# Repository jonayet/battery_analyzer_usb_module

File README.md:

battery_analyzer_usb_module
==============================

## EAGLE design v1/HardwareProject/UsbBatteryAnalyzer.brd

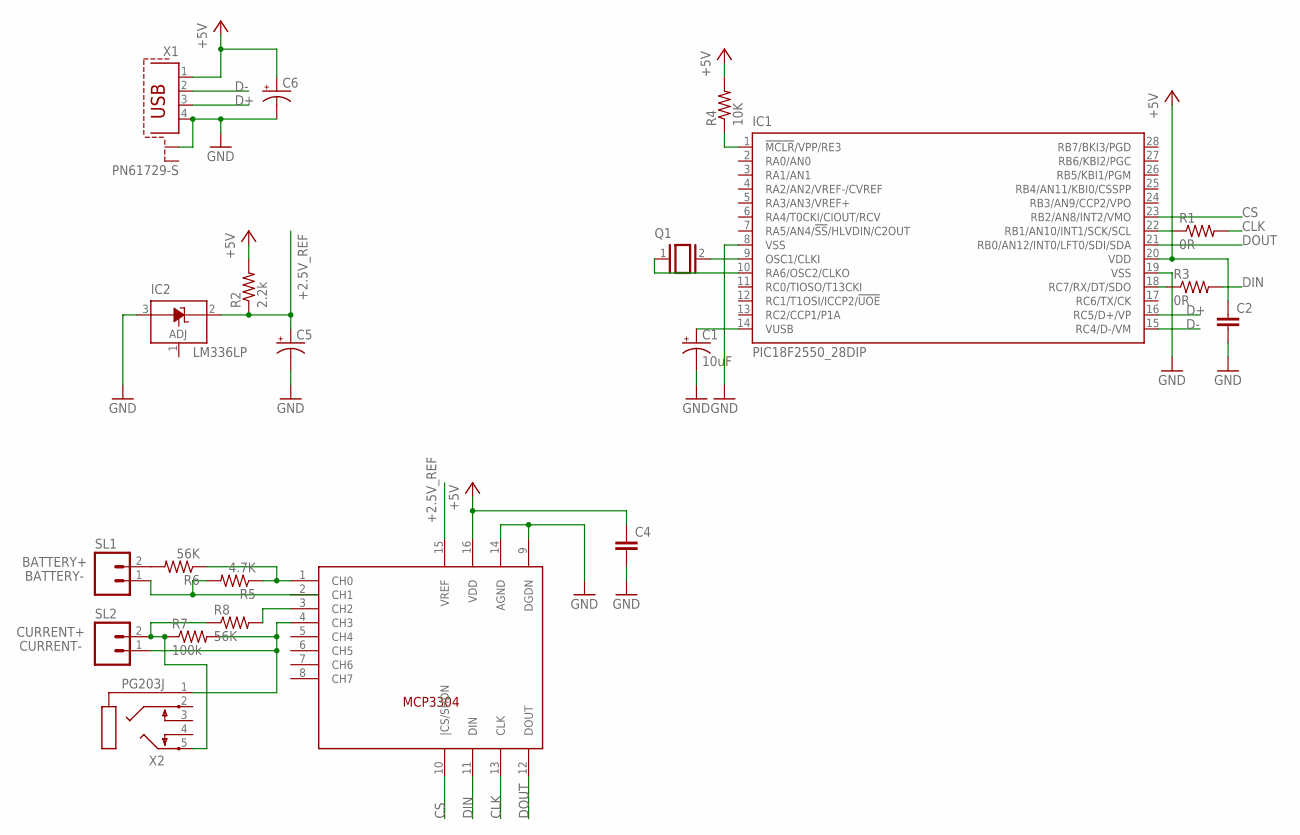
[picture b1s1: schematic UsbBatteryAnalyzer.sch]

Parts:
C1: 10uF; E2,5-7
C2, C4: C-EU050-024X044; C050-024X044
C5, C6: CPOL-USE2.5-7; E2,5-7
IC1: PIC18F2550_28DIP; DIL28-3
IC2: LM336LP; TO92
Q1: XTAL/S; QS
R1: 0R; 0207/5V
R2: 2.2k; 0204/7
R3: 0R; 0207/10
R4: 10K; 0204/7
R5: 4.7K; 0204/7
R6, R8: 56K; 0204/7
R7: 100k; 0204/7
SL1, SL2: M02; 02P
U$1: MCP3304; DIP16
X1: PN61729-S
X2: PG203J

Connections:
+2.5V_REF: C5.+, IC2.2 (C), R2.1, U$1.15 (VREF)
+5V: C2.1, C4.1, C6.+, IC1.20 (VDD), R2.2, R4.2, U$1.16 (VDD), X1.1
BATTERY+: R6.2, SL1.2
BATTERY-: R5.2, SL1.1, U$1.2 (CH1)
CLK: R1.2, U$1.13 (CLK)
CS: IC1.23 (RB2/AN8/INT2/VMO), U$1.10 (|CS/SHDN)
CURRENT+: R7.1, R8.1, SL2.2, X2.5
CURRENT-: R7.2, SL2.1, U$1.4 (CH3), X2.1
D+: IC1.16 (RC5/D+/VP), X1.3
D-: IC1.15 (RC4/D-/VM), X1.2
DIN: R3.2, U$1.11 (DIN)
DOUT: IC1.21 (RB0/AN12/INT0/LFT0/SDI/SDA), U$1.12 (DOUT)
GND: C1.-, C2.2, C4.2, C5.-, C6.-, IC1.8 (VSS), IC1.19 (VSS), IC2.3 (A), U$1.9 (DGDN), U$1.14 (AGND), X1.4, X1.S1
unnamed: IC1.9 (OSC1/CLKI), Q1.2
unnamed: R5.1, R6.1, U$1.1 (CH0)
unnamed: IC1.10 (RA6/OSC2/CLKO), Q1.1
unnamed: C1.+, IC1.14 (VUSB)
unnamed: R8.2, U$1.3 (CH2)
unnamed: IC1.1 (!MCLR!/VPP/RE3), R4.1
unnamed: IC1.22 (RB1/AN10/INT1/SCK/SCL), R1.1
unnamed: IC1.18 (RC7/RX/DT/SDO), R3.1

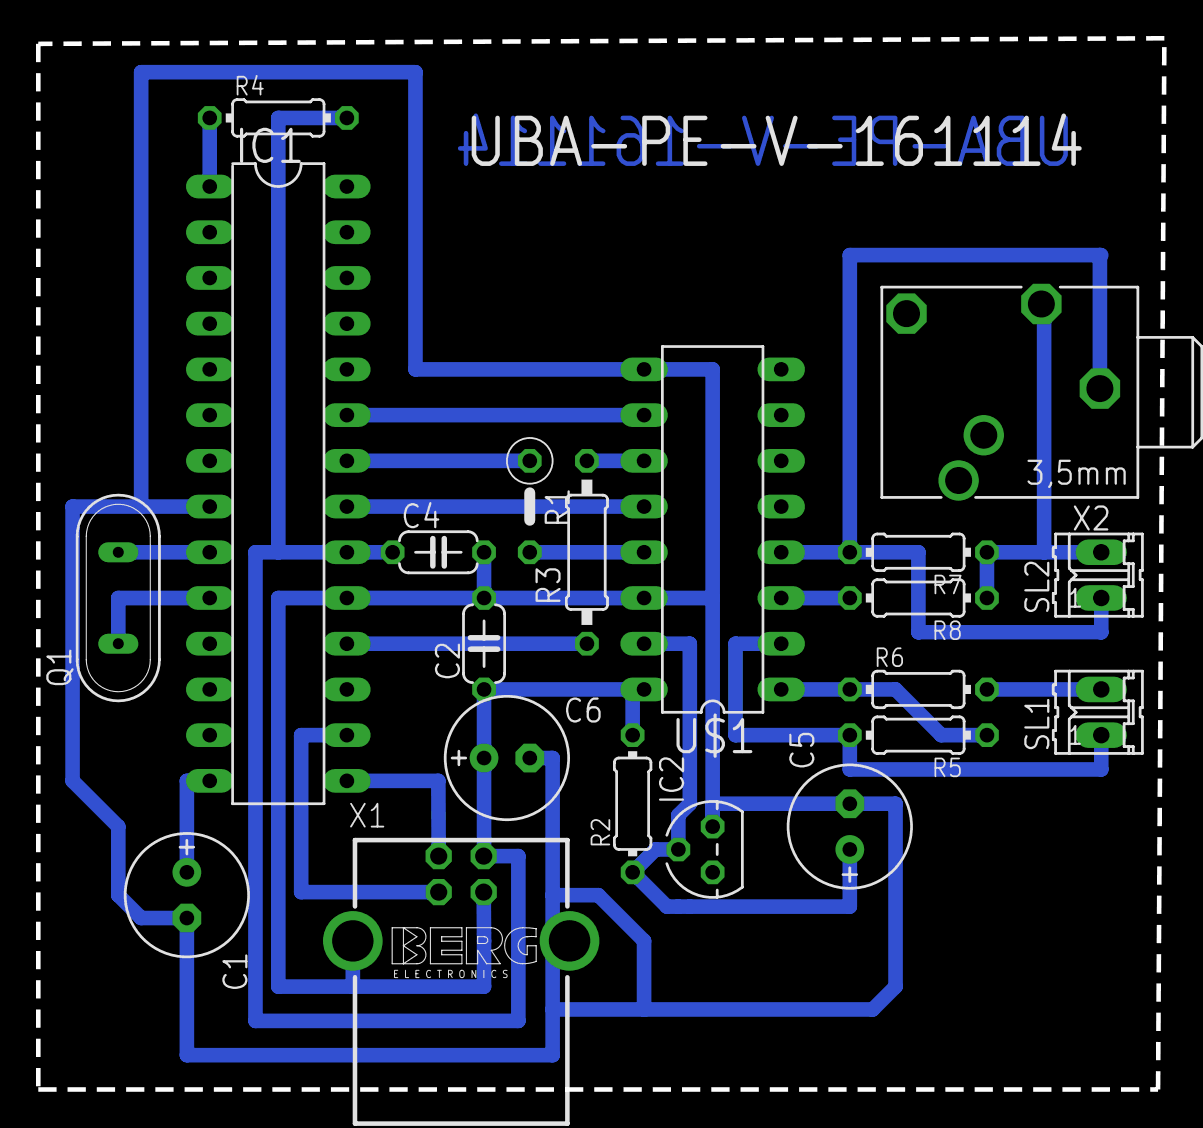
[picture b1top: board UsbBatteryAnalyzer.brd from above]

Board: 2 copper layers, 62.6 x 58.4 mm, 21 parts (0 on the bottom side), 21 nets.
